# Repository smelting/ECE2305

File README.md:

# ECE2305
Repo for team 11's major project.

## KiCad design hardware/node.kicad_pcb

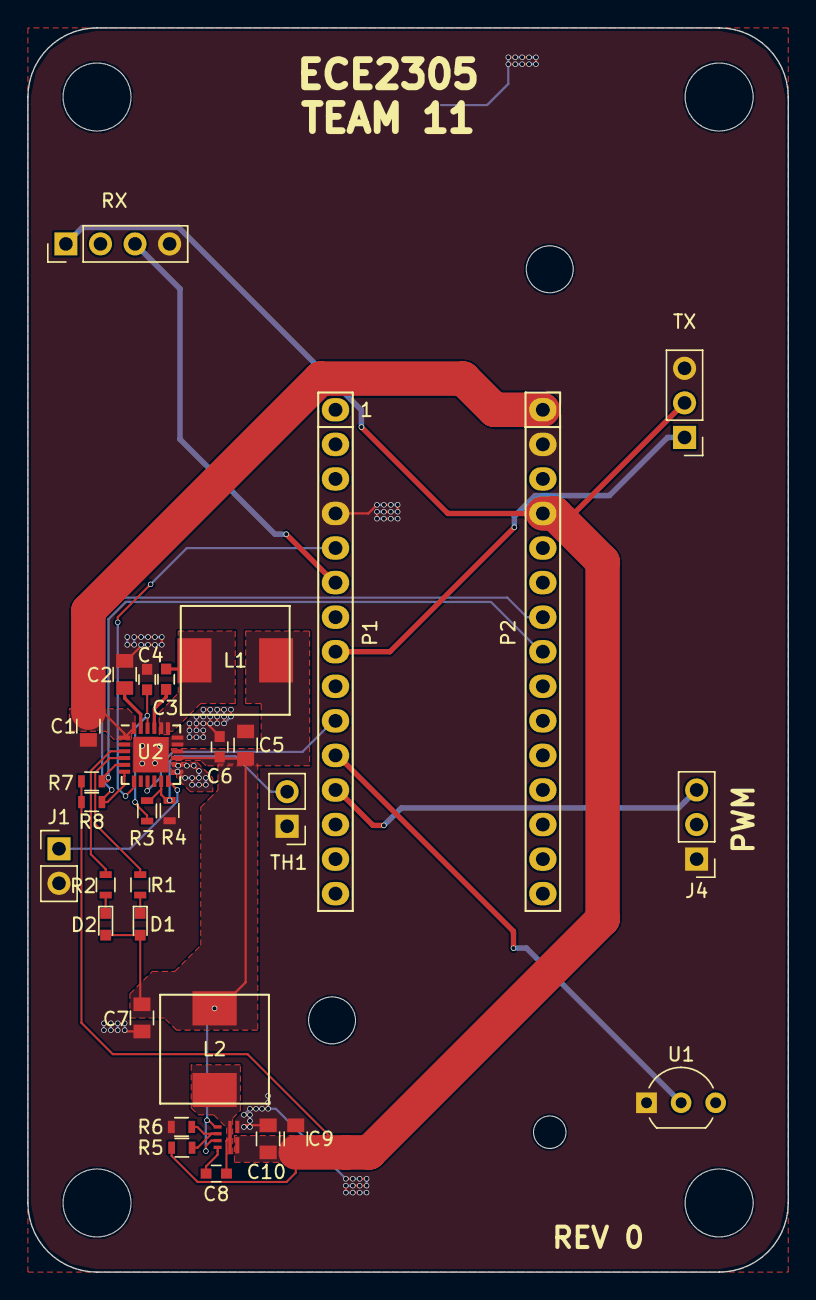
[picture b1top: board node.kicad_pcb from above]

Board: 2 copper layers, 55.9 x 91.4 mm, 33 parts (1 on the bottom side), 27 nets.

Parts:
BT1: 18650; 18650_SMD
C1, C2, C5, C7: 10uF; C_0805
C3: 47nF; C_0603
C4: 4.7uF; C_0603
C6: 1uF; C_0603
C8: 10nF; C_0603
C9, C10: 22uF; C_0805
D1, D2: LED; LED_0603
J1: CONN_01X02; Pin_Header_Straight_1x02_Pitch2.54mm
J4: CONN_01X03; Pin_Header_Straight_1x03_Pitch2.54mm
L1, L2: 1uH; DR73
P1: Digital; Socket_Strip_Arduino_1x15
P2: Analog; Socket_Strip_Arduino_1x15
R1, R2: 2.2k; R_0603
R3: 5.23k; R_0603
R4: 30.1k; R_0603
R5: 316k; R_0603
R6: 100k; R_0603
R7, R8: 10k; R_0603
RX: CONN_01X04; Pin_Header_Straight_1x04_Pitch2.54mm
TH1: 10k; Pin_Header_Straight_1x02_Pitch2.54mm
TX: CONN_01X03; Pin_Header_Straight_1x03_Pitch2.54mm
U1: MAX31820PAR; TO-92_Inline_Wide
U2: bq25601; QFN-24-1EP_4x4mm_Pitch0.5mm
U3: tps61230A; VQFN(7)(2x2mm)

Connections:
+5V: C9.1, C10.1, P2.4, R5.1, R7.2, R8.2, RX.1, TX.2, U3.7
/2: P1.5, U2.7
/3(**): P1.6, RX.2, RX.3
/5(**): P1.8, TX.1
/7: P1.10, U2.9
/8: P1.11, U1.2
/9(**): J4.3, P1.12
/A4: P2.8, R7.1, U2.5
/A5: P2.7, R8.1, U2.6
/Charge/BAT: BT1.1, U2.13, U2.14
/Charge/SYS: C5.2, C6.2, C7.1, D1.2, D2.2, L1.2, L2.1, U2.15, U2.16, U3.2, U3.4
/Reset: P1.3, P2.3
/Vin: C1.2, P2.1, U2.1, U2.24
/Wake: J1.1, U2.12
GND: BT1.2, C1.1, C2.1, C4.1, C5.1, C6.1, C7.2, C9.2, C10.2, J1.2, J4.1, P1.4, P2.2, R4.1, R6.2, RX.4, TH1.1, TX.3, U1.1, U2.2, U2.17, U2.18, U2.25, U3.6
unnamed: C2.2, U2.23
unnamed: C3.1, L1.1, U2.19, U2.20
unnamed: C3.2, U2.21
unnamed: C4.2, R3.2, U2.22
unnamed: C8.1, L2.2, U3.5
unnamed: C8.2, U3.1
unnamed: D1.1, R1.2
unnamed: D2.1, R2.2
unnamed: R1.1, U2.4
unnamed: R2.1, U2.3
unnamed: R3.1, R4.2, TH1.2, U2.11
unnamed: R5.2, R6.1, U3.3

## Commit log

2018-04-09 Initial Commit of board files and gerber plots Boards have already been ordered
2018-04-09 Made register file for battery charger IC The register addresses for the bq25601 have been written
2018-04-19 reads temp
2018-04-19 actually added function for temp
2018-04-26 demo tx and rx
2018-04-26 actually pushed....
2018-04-26 fixed the merge conflict...
